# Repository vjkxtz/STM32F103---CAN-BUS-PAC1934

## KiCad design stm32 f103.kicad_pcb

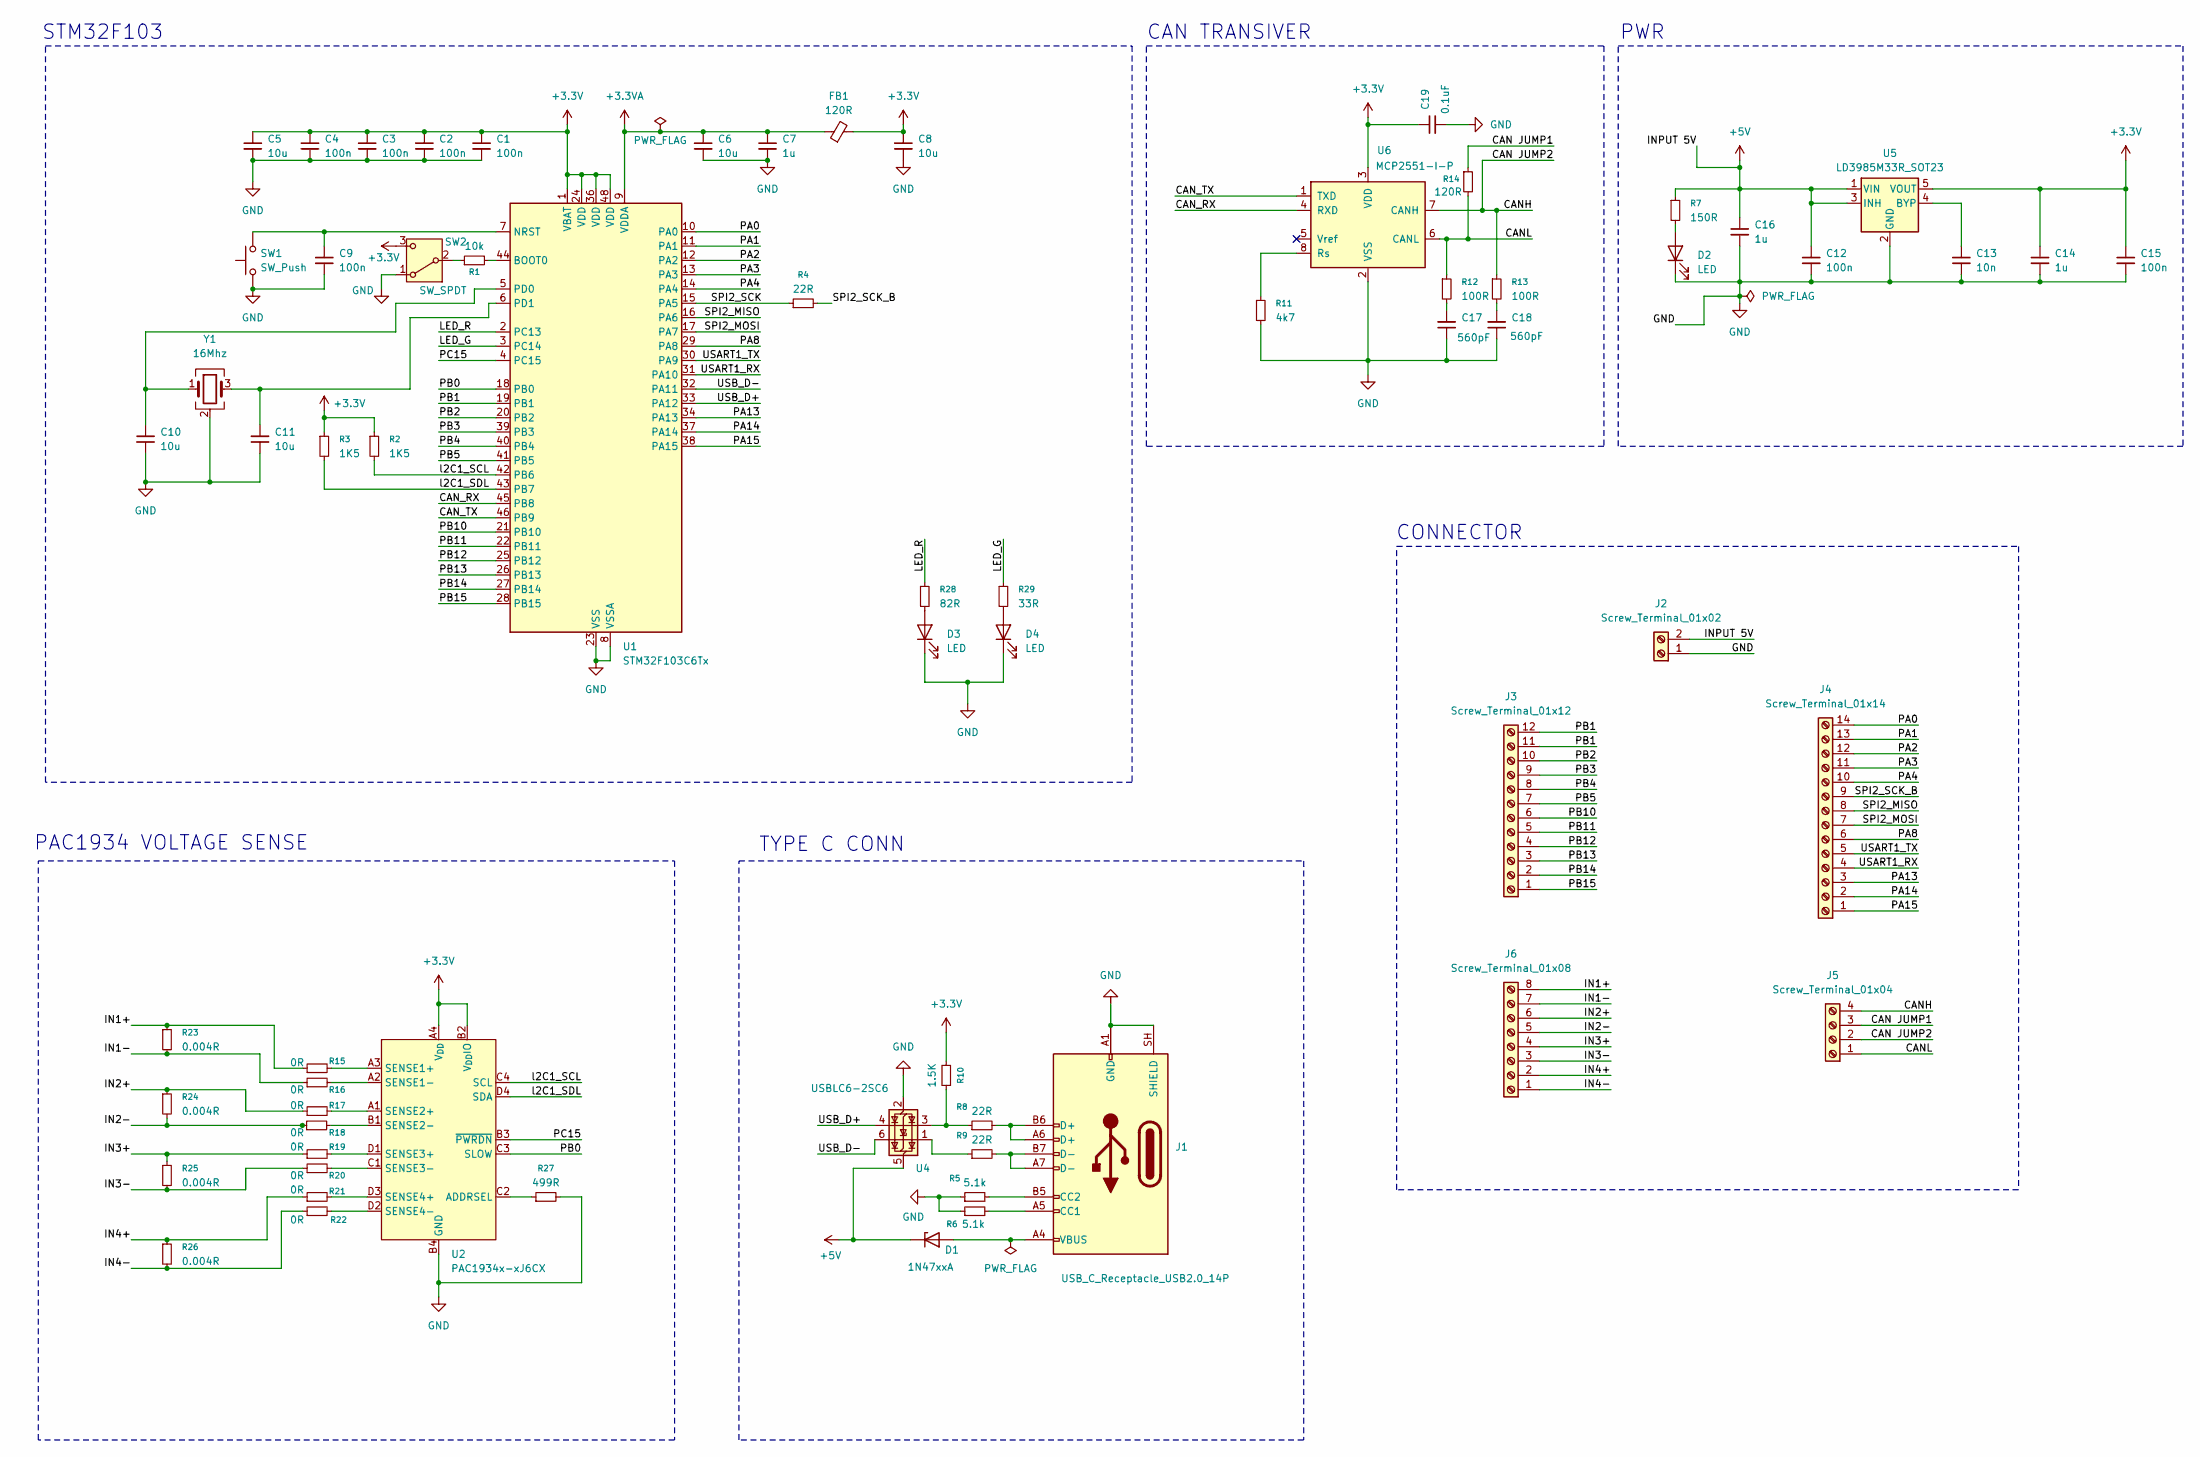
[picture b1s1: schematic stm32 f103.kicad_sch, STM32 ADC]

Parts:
C1, C2, C3, C4, C9, C12, C15: 100n; C_1206_3216Metric
C5, C6, C8, C10, C11: 10u; C_1206_3216Metric
C7, C14, C16: 1u; C_1206_3216Metric
C13: 10n; C_1206_3216Metric
C17, C18: 560pF; C_1206_3216Metric
C19: 0.1uF; C_1206_3216Metric
D1: 1N47xxA; D_1206_3216Metric
D2, D3, D4: LED; LED_1210_3225Metric
FB1: 120R; R_1206_3216Metric
J1: USB_C_Receptacle_USB2.0_14P; USB_C_Receptacle_GCT_USB4115-03-C
J2: Screw_Terminal_01x02; PhoenixContact_MCV_1,5_2-G-3.5_1x02_P3.50mm_Vertical
J3: Screw_Terminal_01x12; PhoenixContact_MCV_1,5_12-G-3.5_1x12_P3.50mm_Vertical
J4: Screw_Terminal_01x14; PhoenixContact_MCV_1,5_14-G-3.5_1x14_P3.50mm_Vertical
J5: Screw_Terminal_01x04; PhoenixContact_MCV_1,5_4-G-3.5_1x04_P3.50mm_Vertical
J6: Screw_Terminal_01x08; PhoenixContact_MCV_1,5_8-G-3.81_1x08_P3.81mm_Vertical
R1: 10k; R_1206_3216Metric
R2, R3: 1K5; R_1206_3216Metric
R4, R8, R9: 22R; R_1206_3216Metric
R5, R6: 5.1k; R_1206_3216Metric
R7: 150R; R_1206_3216Metric
R10: 1.5K; R_1206_3216Metric
R11: 4k7; R_1206_3216Metric
R12, R13: 100R; R_1206_3216Metric
R14: 120R; R_1206_3216Metric
R15, R16, R17, R18, R19, R20, R21, R22: 0R; R_1206_3216Metric
R23, R24, R25, R26: 0.004R; R_1206_3216Metric
R27: 499R; R_1206_3216Metric
R28: 82R; R_1206_3216Metric
R29: 33R; R_1206_3216Metric
SW1: SW_Push; SW_Push_1P1T_NO_Vertical_Wuerth_434133025816
SW2: SW_SPDT; SW_SPDT_PCM12
U1: STM32F103C6Tx; LQFP-48_7x7mm_P0.5mm
U2: PAC1934x-xJ6CX; WLCSP-16_2.225x2.17mm_Layout4x4_P0.5mm
U4: USBLC6-2SC6; SOT-23-6
U5: LD3985M33R_SOT23; SOT-23-5
U6: MCP2551-I-P; DIP-8_W7.62mm
Y1: 16Mhz; Crystal_SMD_3225-4Pin_3.2x2.5mm

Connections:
+3.3V: C1.1, C2.1, C3.1, C4.1, C5.1, C8.1, C14.2, C15.1, C19.1, FB1.2, R2.1, R3.1, R10.2, SW2.3 (C), U1.1 (VBAT), U1.24 (VDD), U1.36 (VDD), U1.48 (VDD), U2.A4 (V_{DD}), U2.B2 (V_{DD}IO), U5.5 (VOUT), U6.3 (VDD)
+3.3VA: C6.1, C7.1, FB1.1, U1.9 (VDDA)
+5V: C12.1, C16.1, D1.1 (K), J2.2, R7.1, U4.5 (VBUS), U5.1 (VIN), U5.3 (INH)
/CAN JUMP1: J5.3, R14.1
/CAN JUMP2: J5.2, J5.4, R13.1, U6.7 (CANH)
/CANL: J5.1, R12.1, R14.2, U6.6 (CANL)
/CAN_RX: U1.45 (PB8), U6.4 (RXD)
/CAN_TX: U1.46 (PB9), U6.1 (TXD)
/IN1+: J6.8, R15.1, R23.1
/IN1-: J6.7, R16.1, R23.2
/IN2+: J6.6, R17.1, R24.1
/IN2-: J6.5, R18.1, R24.2
/IN3+: J6.4, R19.1, R25.1
/IN3-: J6.3, R20.1, R25.2
/IN4+: J6.2, R21.1, R26.1
/IN4-: J6.1, R22.1, R26.2
/LED_G: R29.1, U1.3 (PC14)
/LED_R: R28.1, U1.2 (PC13)
/PA0: J4.14, U1.10 (PA0)
/PA1: J4.13, U1.11 (PA1)
/PA2: J4.12, U1.12 (PA2)
/PA3: J4.11, U1.13 (PA3)
/PA4: J4.10, U1.14 (PA4)
/PA8: J4.6, U1.29 (PA8)
/PA13: J4.3, U1.34 (PA13)
/PA14: J4.2, U1.37 (PA14)
/PA15: J4.1, U1.38 (PA15)
/PB0: U1.18 (PB0), U2.C3 (SLOW)
/PB1: J3.11, J3.12, U1.19 (PB1)
/PB2: J3.10, U1.20 (PB2)
/PB3: J3.9, U1.39 (PB3)
/PB4: J3.8, U1.40 (PB4)
/PB5: J3.7, U1.41 (PB5)
/PB10: J3.6, U1.21 (PB10)
/PB11: J3.5, U1.22 (PB11)
/PB12: J3.4, U1.25 (PB12)
/PB13: J3.3, U1.26 (PB13)
/PB14: J3.2, U1.27 (PB14)
/PB15: J3.1, U1.28 (PB15)
/PC15: U1.4 (PC15), U2.B3 (~PWRDN)
/SPI2_MISO: J4.8, U1.16 (PA6)
/SPI2_MOSI: J4.7, U1.17 (PA7)
/SPI2_SCK: R4.1, U1.15 (PA5)
/SPI2_SCK_B: J4.9, R4.2
/USART1_RX: J4.4, U1.31 (PA10)
/USART1_TX: J4.5, U1.30 (PA9)
/USB_D+: U1.33 (PA12), U4.4 (I/O2)
/USB_D-: U1.32 (PA11), U4.6 (I/O1)
/l2C1_SCL: R2.2, U1.42 (PB6), U2.C4 (SCL)
/l2C1_SDL: R3.2, U1.43 (PB7), U2.D4 (SDA)
GND: C1.2, C2.2, C3.2, C4.2, C5.2, C6.2, C7.2, C8.2, C9.2, C10.2, C11.2, C12.2, C13.2, C14.1, C15.2, C16.2, C17.2, C18.2, C19.2, D2.1 (K), D3.1 (K), D4.1 (K), J1.A1 (GND), J1.A12 (GND), J1.B1 (GND), J1.B12 (GND), J1.SH (SHIELD), J2.1, R5.1, R6.1, R11.2, R27.2, SW1.1, SW2.1 (A), U1.8 (VSSA), U1.23 (VSS), U1.35 (VSS), U1.47 (VSS), U2.B4 (GND), U4.2 (GND), U5.2 (GND), U6.2 (VSS), Y1.2 (G), Y1.4 (G)
unnamed: C17.1, R12.2
unnamed: C18.1, R13.2
unnamed: D1.2 (A), J1.A4 (VBUS), J1.A9 (VBUS), J1.B4 (VBUS), J1.B9 (VBUS)
unnamed: D2.2 (A), R7.2
unnamed: D3.2 (A), R28.2
unnamed: D4.2 (A), R29.2
unnamed: J1.A5 (CC1), R6.2
unnamed: J1.B5 (CC2), R5.2
unnamed: J1.A6 (D+), J1.B6 (D+), R8.2
unnamed: J1.A7 (D-), J1.B7 (D-), R9.2
unnamed: R9.1, U4.1 (I/O1)
unnamed: R8.1, R10.1, U4.3 (I/O2)
unnamed: R1.1, SW2.2 (B)
unnamed: R1.2, U1.44 (BOOT0)
unnamed: C9.1, SW1.2, U1.7 (NRST)
unnamed: C10.1, U1.5 (PD0), Y1.1
unnamed: C11.1, U1.6 (PD1), Y1.3
unnamed: R27.1, U2.C2 (ADDRSEL)
unnamed: R15.2, U2.A3 (SENSE1+)
unnamed: R16.2, U2.A2 (SENSE1-)
unnamed: R17.2, U2.A1 (SENSE2+)
unnamed: R18.2, U2.B1 (SENSE2-)
unnamed: R19.2, U2.D1 (SENSE3+)
unnamed: R20.2, U2.C1 (SENSE3-)
unnamed: R21.2, U2.D3 (SENSE4+)
unnamed: R22.2, U2.D2 (SENSE4-)
unnamed: C13.1, U5.4 (BYP)
unnamed: R11.1, U6.8 (Rs)

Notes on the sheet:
CONNECTOR
PWR
PAC1934 VOLTAGE SENSE
CAN TRANSIVER
STM32F103
TYPE C CONN

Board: 2 copper layers, 67 parts (0 on the bottom side), 79 nets, no tracks yet.
